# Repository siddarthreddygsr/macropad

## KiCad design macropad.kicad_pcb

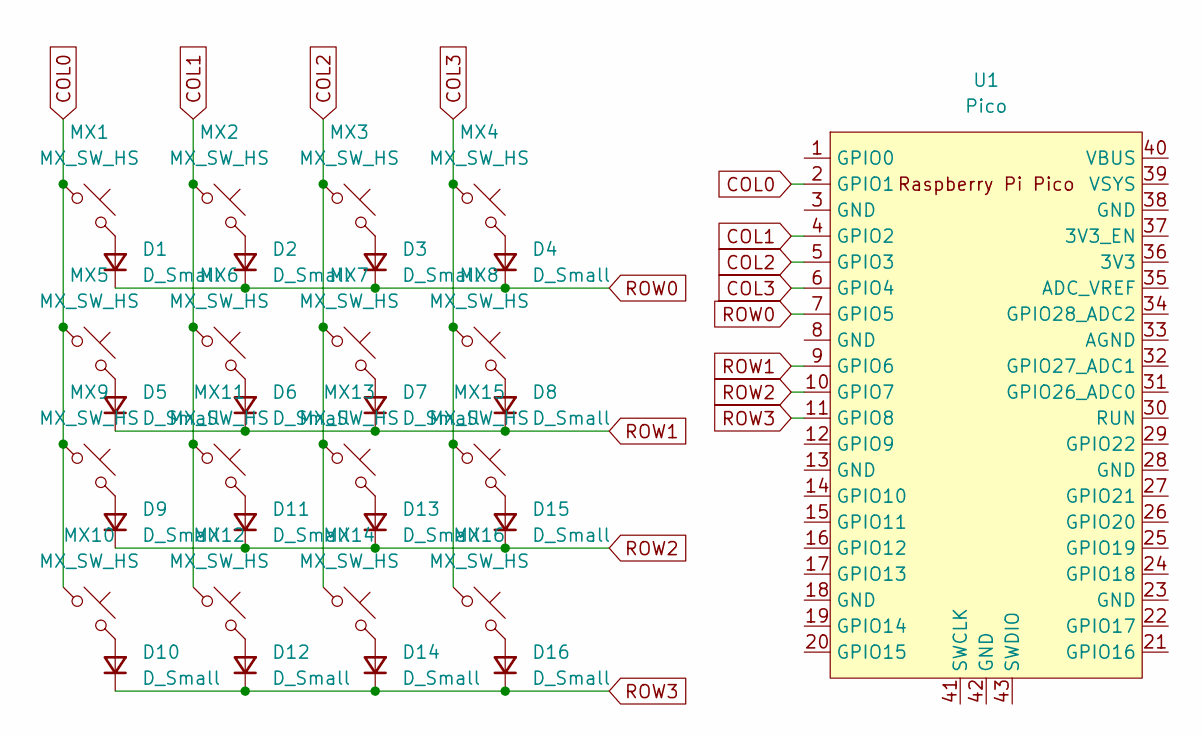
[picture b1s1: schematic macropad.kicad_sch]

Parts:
D1, D2, D3, D4, D5, D6, D7, D8, D9, D10, D11, D12, D13, D14, D15, D16: D_Small; D_SOD-123
MX1, MX2, MX3, MX4, MX5, MX6, MX7, MX8, MX9, MX10, MX11, MX12, MX13, MX14, MX15, MX16: MX_SW_HS; SW_MX_HS_CPG151101S11_1u
U1: Pico; RPi_Pico_SMD_TH

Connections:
COL0: MX1.1, MX5.1, MX9.1, MX10.1, U1.2 (GPIO1)
COL1: MX2.1, MX6.1, MX11.1, MX12.1, U1.4 (GPIO2)
COL2: MX3.1, MX7.1, MX13.1, MX14.1, U1.5 (GPIO3)
COL3: MX4.1, MX8.1, MX15.1, MX16.1, U1.6 (GPIO4)
unnamed: D1.2 (A), MX1.2
unnamed: D2.2 (A), MX2.2
unnamed: D3.2 (A), MX3.2
unnamed: D4.2 (A), MX4.2
unnamed: D5.2 (A), MX5.2
unnamed: D6.2 (A), MX6.2
unnamed: D7.2 (A), MX7.2
unnamed: D8.2 (A), MX8.2
unnamed: D9.2 (A), MX9.2
unnamed: D10.2 (A), MX10.2
unnamed: D11.2 (A), MX11.2
unnamed: D12.2 (A), MX12.2
unnamed: D13.2 (A), MX13.2
unnamed: D14.2 (A), MX14.2
unnamed: D15.2 (A), MX15.2
unnamed: D16.2 (A), MX16.2
ROW0: D1.1 (K), D2.1 (K), D3.1 (K), D4.1 (K), U1.7 (GPIO5)
ROW1: D5.1 (K), D6.1 (K), D7.1 (K), D8.1 (K), U1.9 (GPIO6)
ROW2: D9.1 (K), D11.1 (K), D13.1 (K), D15.1 (K), U1.10 (GPIO7)
ROW3: D10.1 (K), D12.1 (K), D14.1 (K), D16.1 (K), U1.11 (GPIO8)

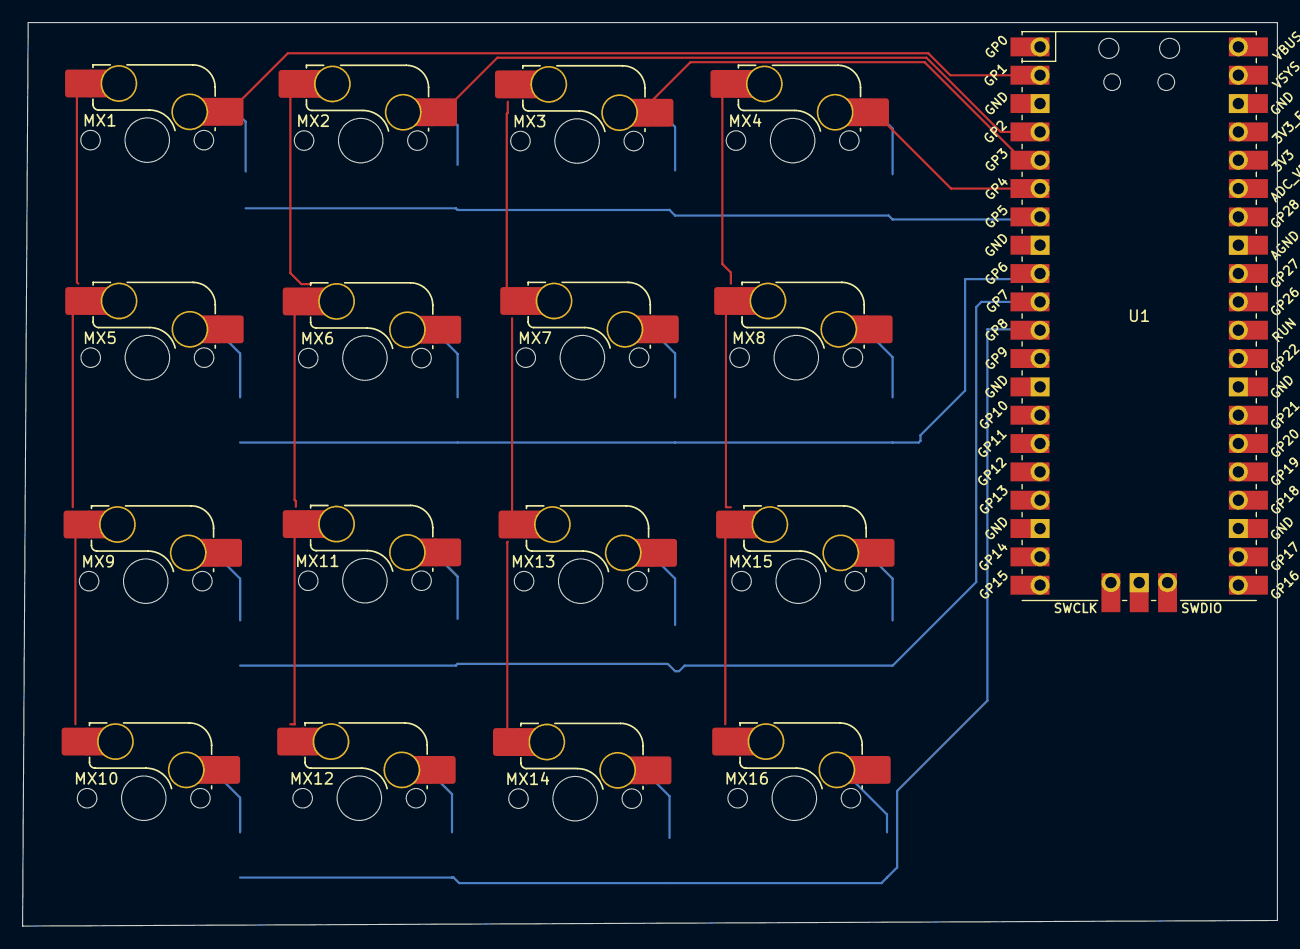
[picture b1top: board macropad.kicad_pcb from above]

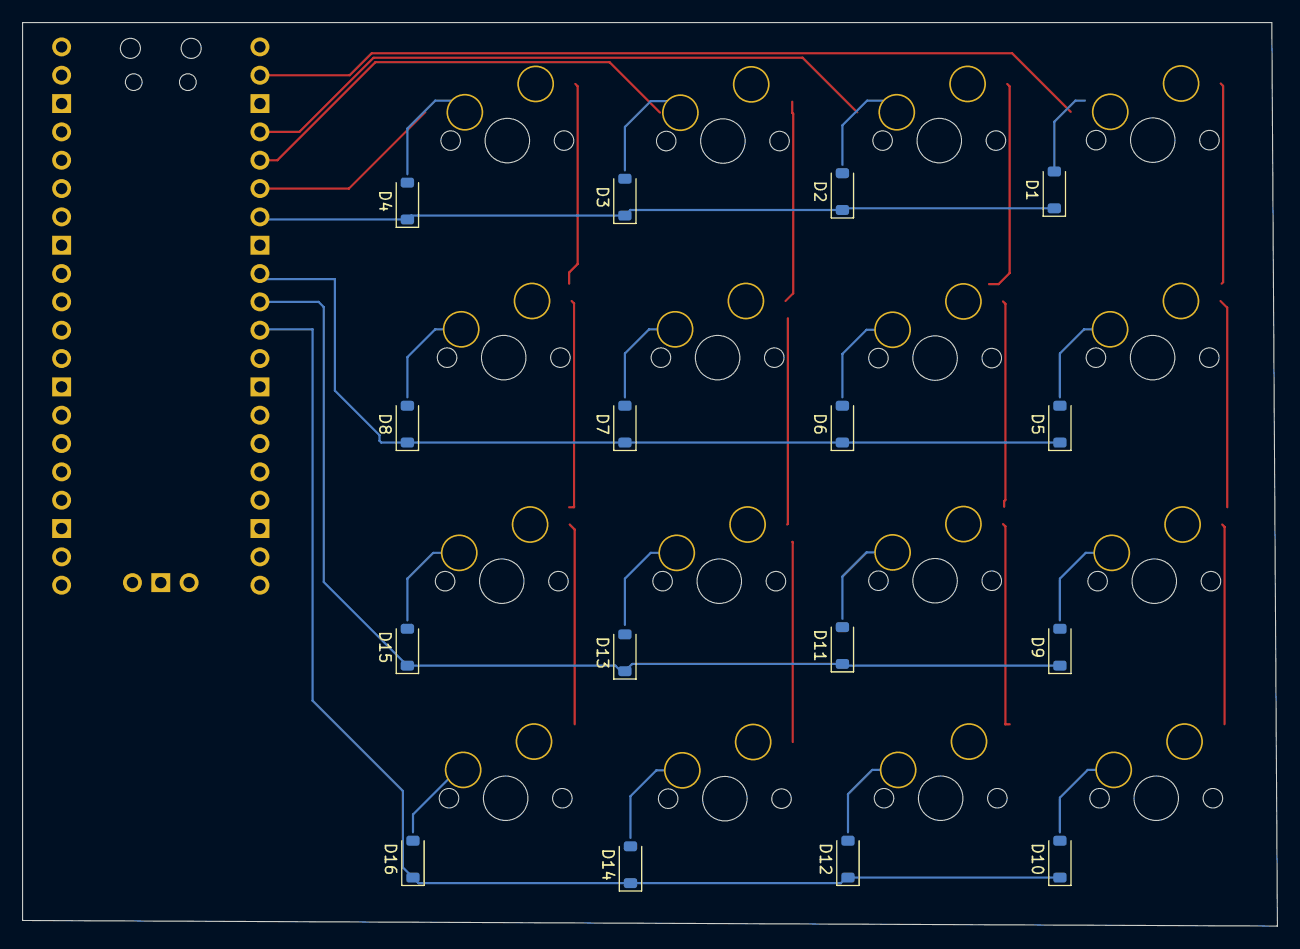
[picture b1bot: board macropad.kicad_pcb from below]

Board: 2 copper layers, 112.5 x 81.0 mm, 33 parts (16 on the bottom side), 24 nets.

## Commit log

2024-08-31 added PCB
2024-08-31 added modules
